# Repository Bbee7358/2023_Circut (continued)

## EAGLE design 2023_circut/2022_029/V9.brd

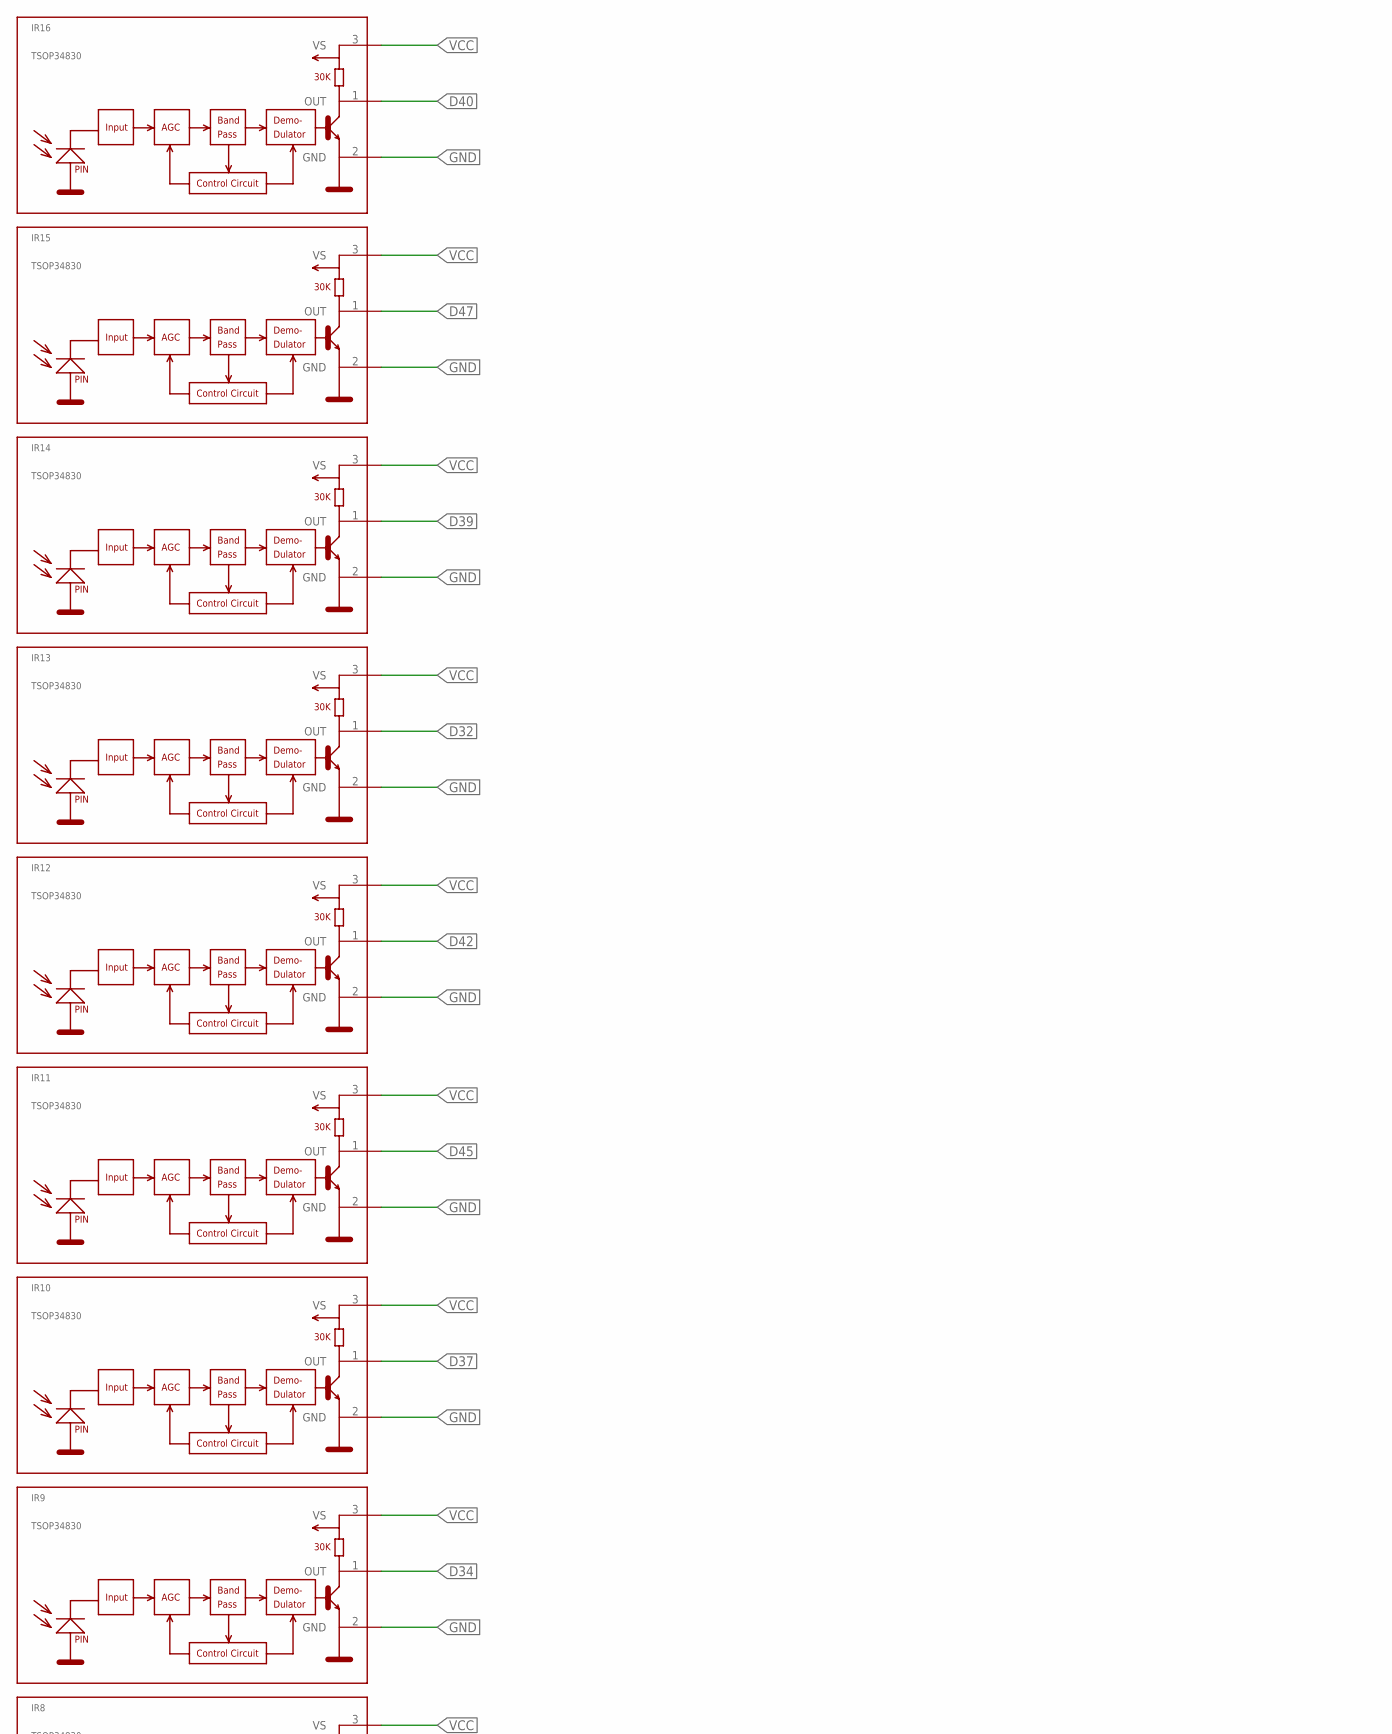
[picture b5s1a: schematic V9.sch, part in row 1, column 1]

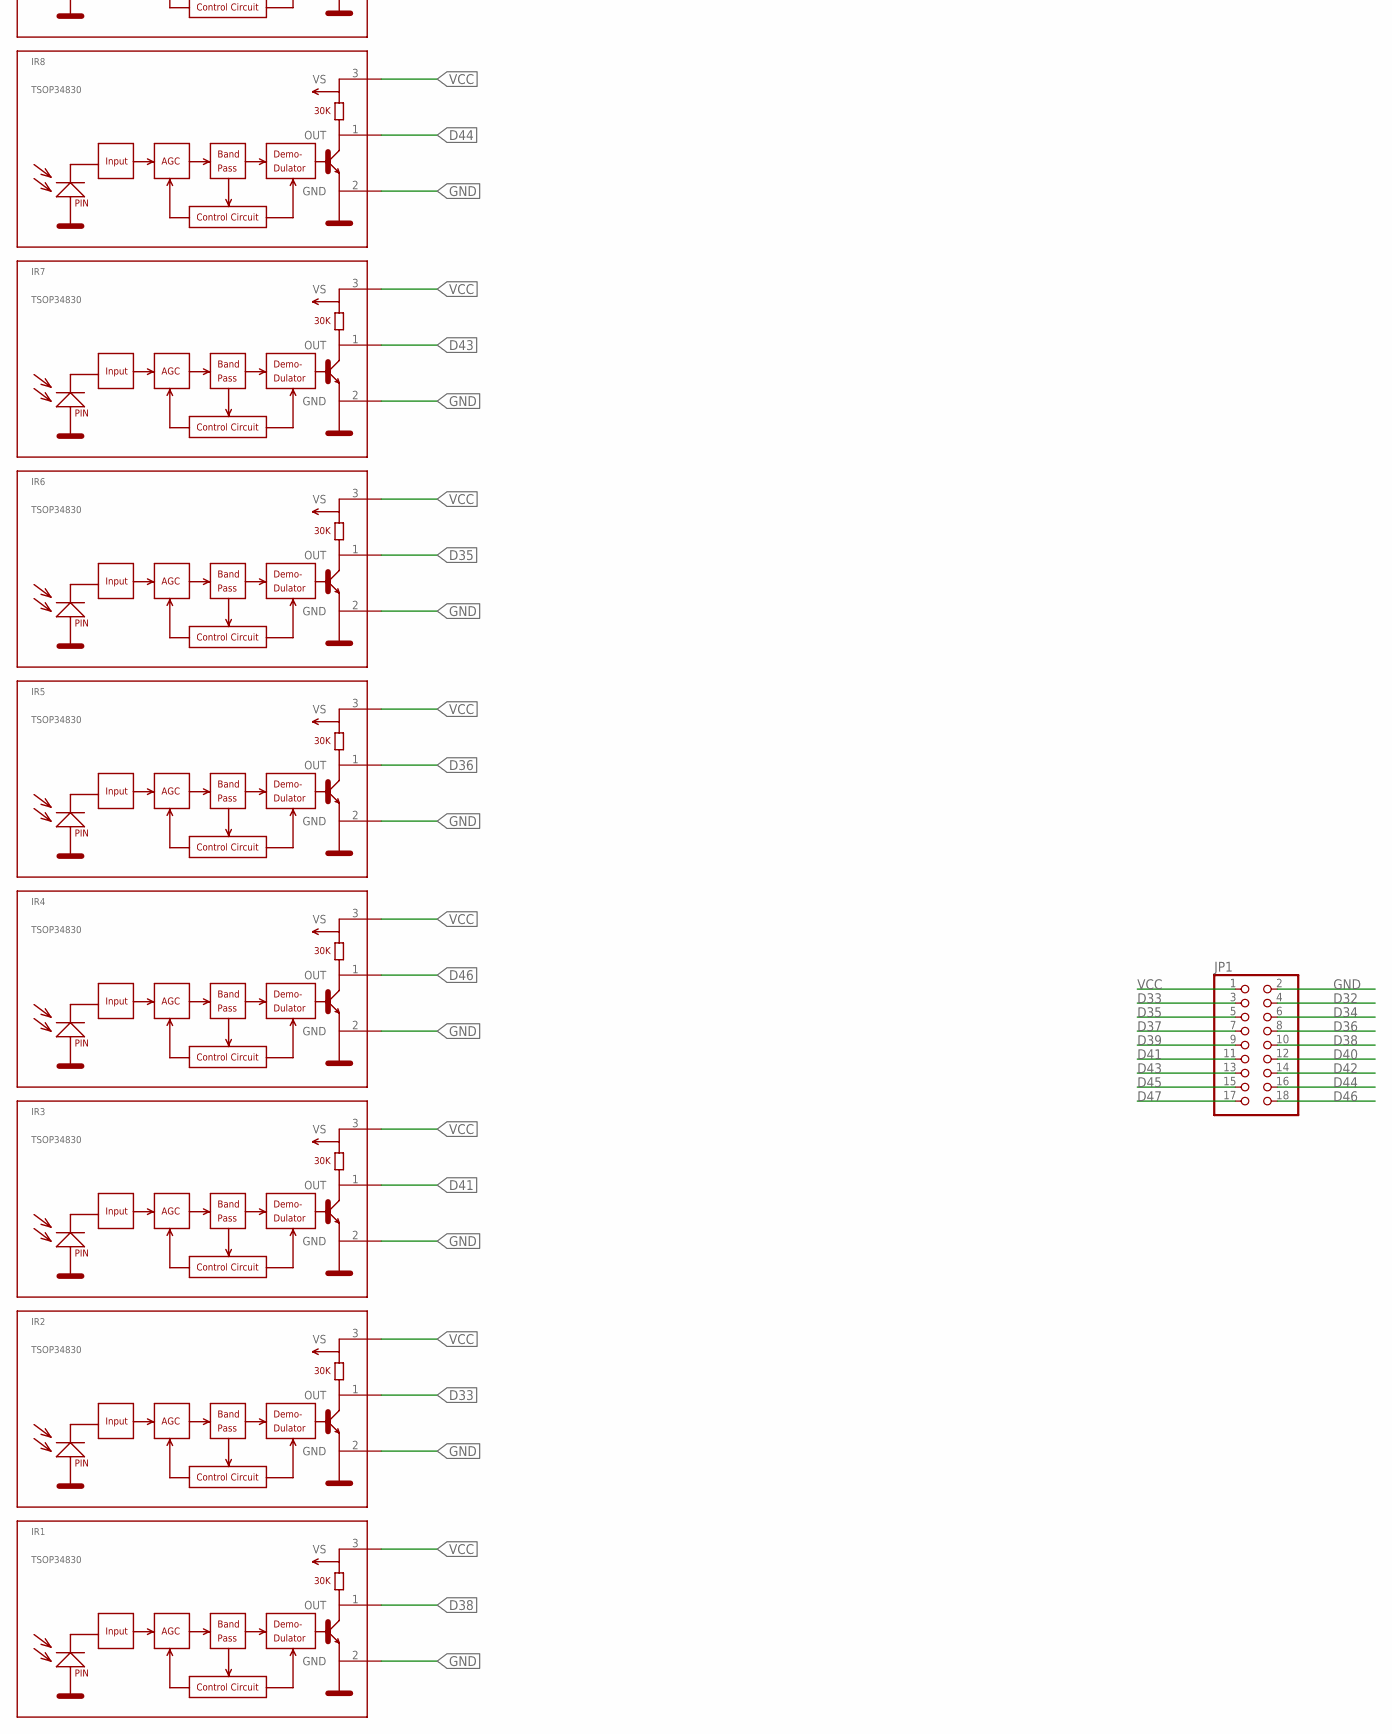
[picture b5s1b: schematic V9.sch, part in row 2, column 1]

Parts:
IR1, IR2, IR3, IR4, IR5, IR6, IR7, IR8, IR9, IR10, IR11, IR12, IR13, IR14, IR15, IR16: TSOP34830; TSOP348
JP1: PINHD-2X09_2.54; 2X09

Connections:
D32: IR13.1 (OUT), JP1.4
D33: IR2.1 (OUT), JP1.3
D34: IR9.1 (OUT), JP1.6
D35: IR6.1 (OUT), JP1.5
D36: IR5.1 (OUT), JP1.8
D37: IR10.1 (OUT), JP1.7
D38: IR1.1 (OUT), JP1.10
D39: IR14.1 (OUT), JP1.9
D40: IR16.1 (OUT), JP1.12
D41: IR3.1 (OUT), JP1.11
D42: IR12.1 (OUT), JP1.14
D43: IR7.1 (OUT), JP1.13
D44: IR8.1 (OUT), JP1.16
D45: IR11.1 (OUT), JP1.15
D46: IR4.1 (OUT), JP1.18
D47: IR15.1 (OUT), JP1.17
GND: IR1.2 (GND), IR2.2 (GND), IR3.2 (GND), IR4.2 (GND), IR5.2 (GND), IR6.2 (GND), IR7.2 (GND), IR8.2 (GND), IR9.2 (GND), IR10.2 (GND), IR11.2 (GND), IR12.2 (GND), IR13.2 (GND), IR14.2 (GND), IR15.2 (GND), IR16.2 (GND), JP1.2
VCC: IR1.3 (VS), IR2.3 (VS), IR3.3 (VS), IR4.3 (VS), IR5.3 (VS), IR6.3 (VS), IR7.3 (VS), IR8.3 (VS), IR9.3 (VS), IR10.3 (VS), IR11.3 (VS), IR12.3 (VS), IR13.3 (VS), IR14.3 (VS), IR15.3 (VS), IR16.3 (VS), JP1.1

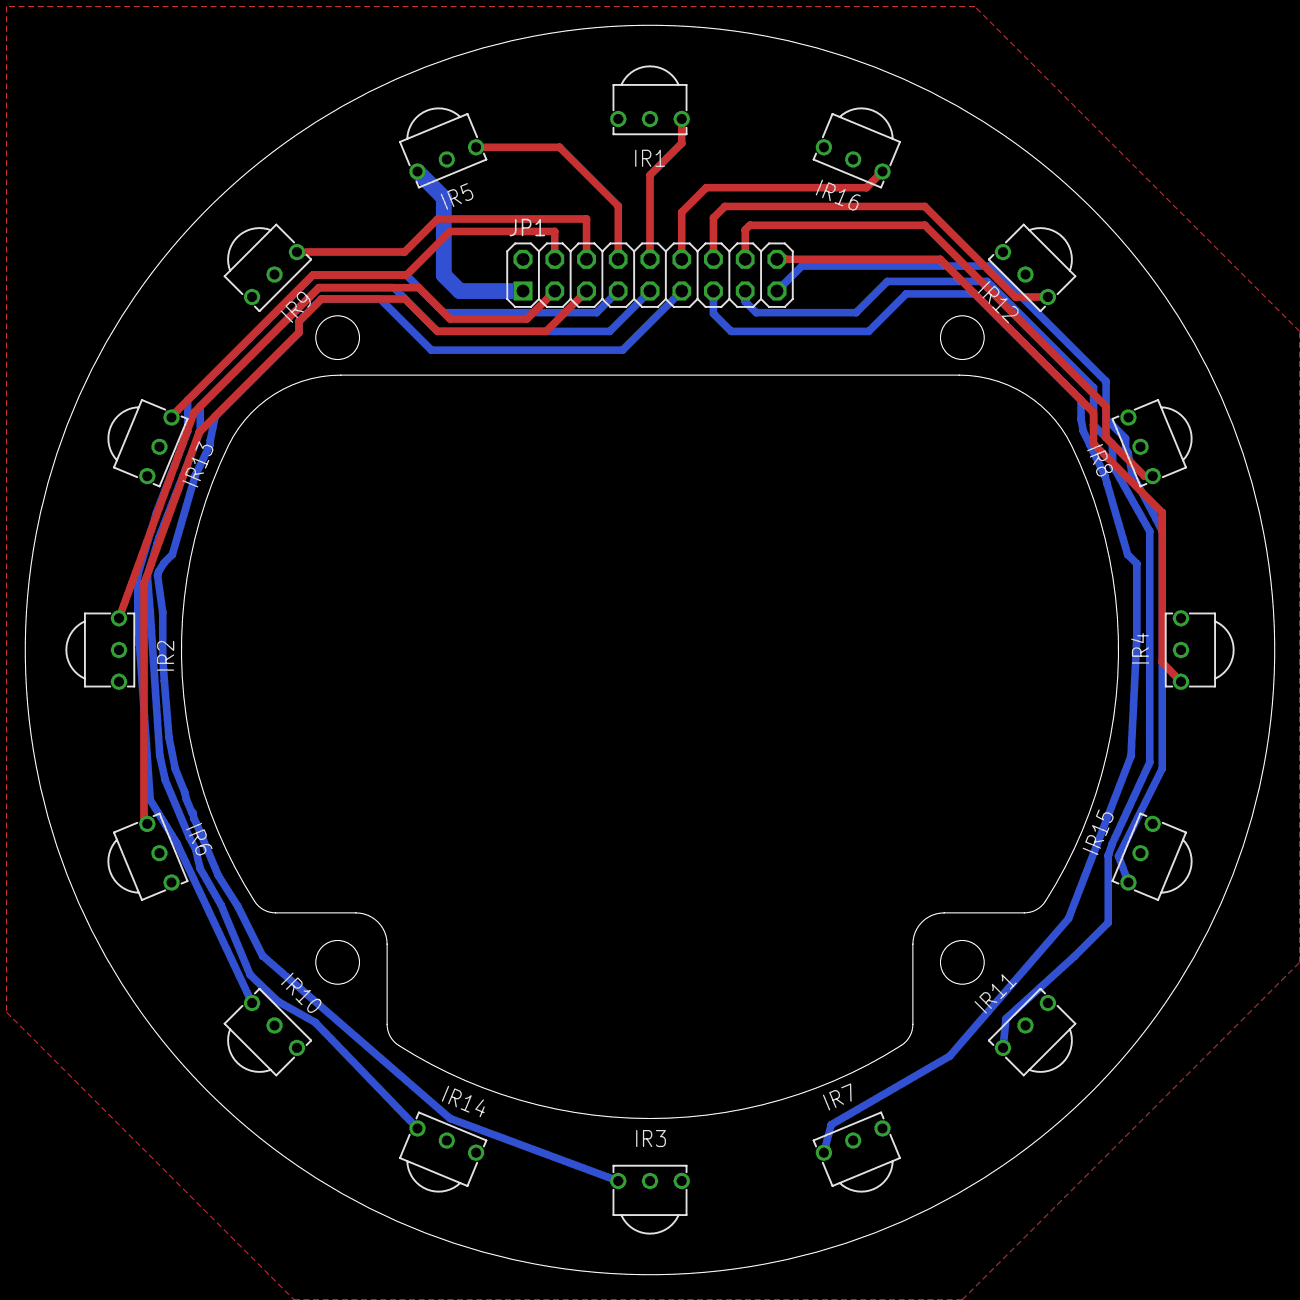
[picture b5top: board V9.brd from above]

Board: 2 copper layers, 100.0 x 100.0 mm, 17 parts (0 on the bottom side), 18 nets.

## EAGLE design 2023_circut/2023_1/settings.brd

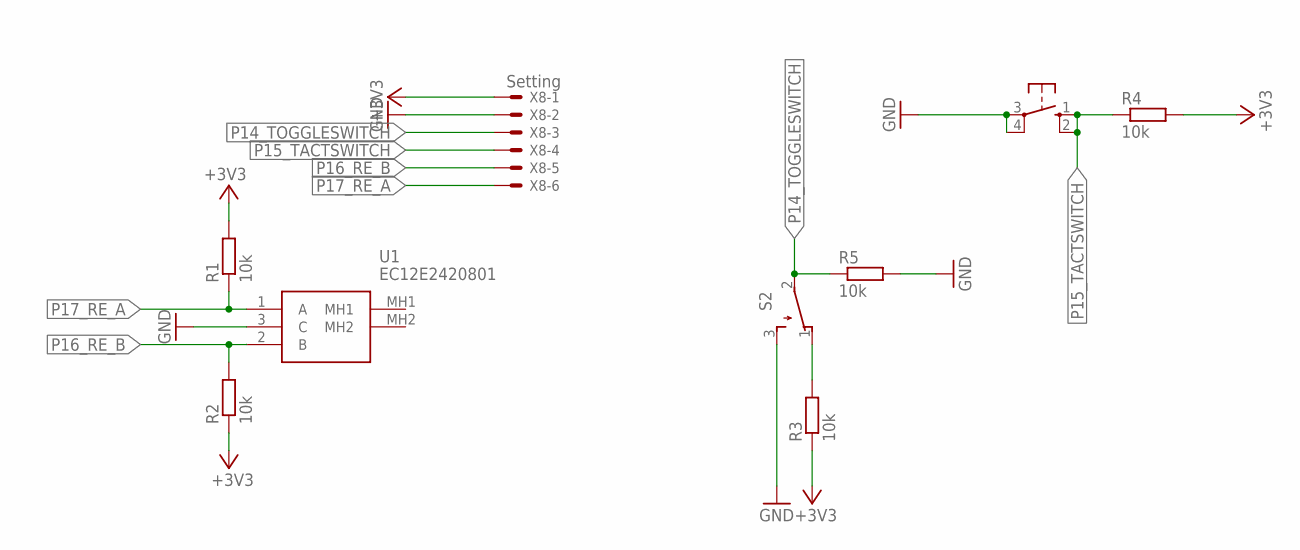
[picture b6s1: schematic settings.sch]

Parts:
R1, R2, R3, R4, R5: 10k; R0603
S1: 40-XX; B3F-40XX
S2: TL32PO; TL3XPO
U1: EC12E2420801
X8: Setting; JST-XH-06-PACKAGE-ROUND-PAD

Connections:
+3V3: R1.2, R2.1, R3.1, R4.2, X8.1
GND: R5.2, S1.3, S1.4 (P1), S2.3 (S), U1.3 (C), X8.2
unnamed: R3.2, S2.1 (O)
P14_TOGGLESWITCH: R5.1, S2.2, X8.3
P15_TACTSWITCH: R4.1, S1.1 (S), S1.2 (S1), X8.4
P16_RE_B: R2.2, U1.2 (B), X8.5
P17_RE_A: R1.1, U1.1 (A), X8.6

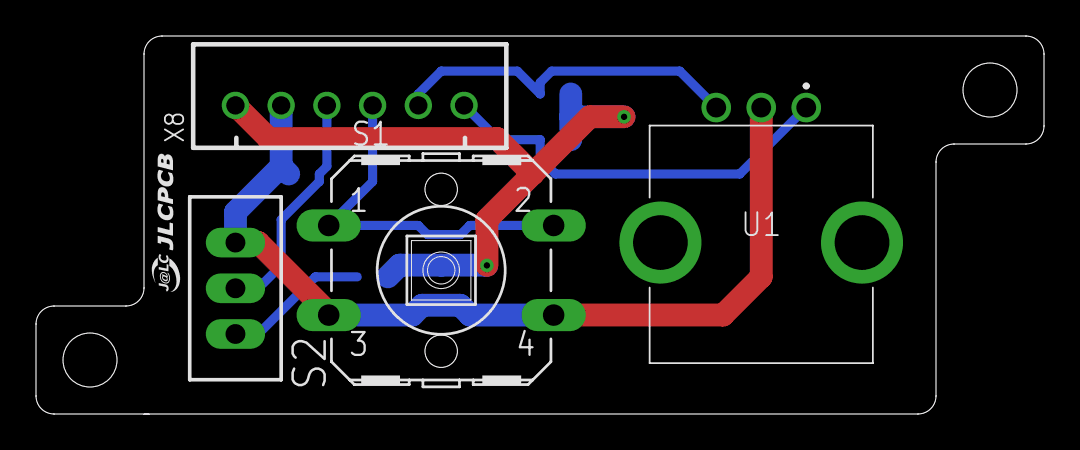
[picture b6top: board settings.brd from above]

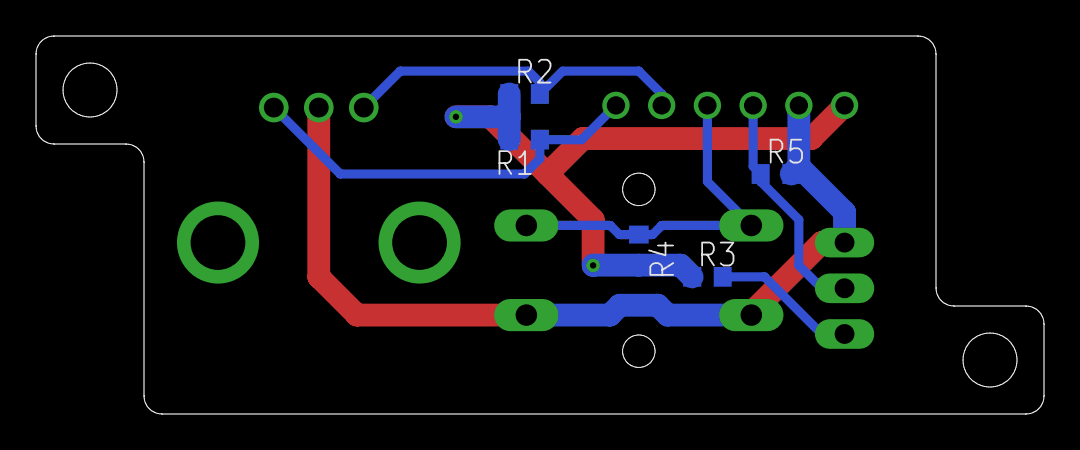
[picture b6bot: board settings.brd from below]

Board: 2 copper layers, 56.0 x 21.0 mm, 9 parts (5 on the bottom side), 7 nets.

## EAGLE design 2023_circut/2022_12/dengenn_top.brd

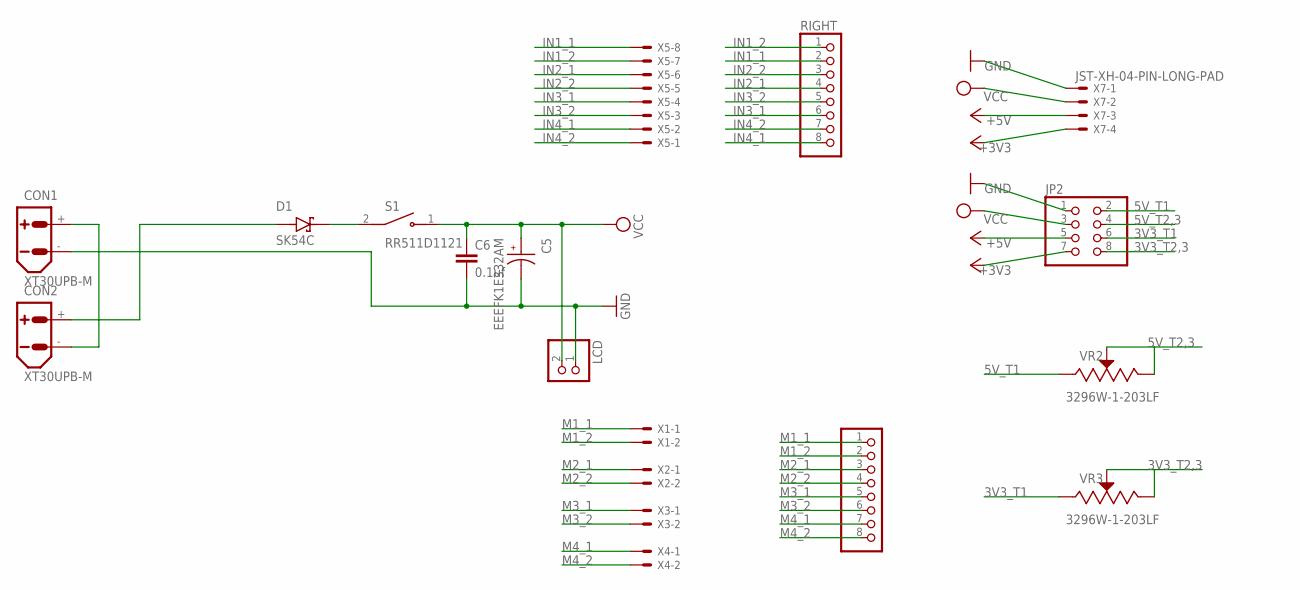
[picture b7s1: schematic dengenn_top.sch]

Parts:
C5: EEEFK1E332AM; CAP_EEEFK1E332AM
C6: 0.1uf; C0603
CON1, CON2: XT30UPB-M
D1: SK54C; DIOM6859X262N
JP2: PINHD-2X4; 2X04
LCD: PINHD-1X2; 1X02
LEFT: PINHD-1X8; 1X08
RIGHT: PINHD-1X8; 1X08
S1: RR511D1121; E-SWITCH_RR511D1121
VR2, VR3: 3296W-1-203LF; TRIM_3296W-1-203LF
X1, X2, X3, X4: JST-XH-02-PIN-LONG-PAD; JST-XH-02-PACKAGE-LONG-PAD
X5: JST-XH-08-PIN-ROUND-PAD; JST-XH-08-PACKAGE-ROUND-PAD
X7: JST-XH-04-PIN-LONG-PAD; JST-XH-04-PACKAGE-LONG-PAD

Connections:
3V3_T1: JP2.6, VR3.1 (CCW)
3V3_T2,3: JP2.8, VR3.2 (WIPER), VR3.3 (CW)
5V_T1: JP2.2, VR2.1 (CCW)
5V_T2,3: JP2.4, VR2.2 (WIPER), VR2.3 (CW)
+3V3: JP2.7, X7.4
+5V: JP2.5, X7.3
GND: C5.2, C6.2, CON1.-, JP2.1, LCD.1, X7.1
IN1_1: RIGHT.2, X5.8
IN1_2: RIGHT.1, X5.7
IN2_1: RIGHT.4, X5.6
IN2_2: RIGHT.3, X5.5
IN3_1: RIGHT.6, X5.4
IN3_2: RIGHT.5, X5.3
IN4_1: RIGHT.8, X5.2
IN4_2: RIGHT.7, X5.1
M1_1: LEFT.1, X1.1
M1_2: LEFT.2, X1.2
M2_1: LEFT.3, X2.1
M2_2: LEFT.4, X2.2
M3_1: LEFT.5, X3.1
M3_2: LEFT.6, X3.2
M4_1: LEFT.7, X4.1
M4_2: LEFT.8, X4.2
unnamed: CON1.+, CON2.-
unnamed: CON2.+, D1.A
unnamed: D1.C (K), S1.2 (COM)
VCC: C5.1, C6.1, JP2.3, LCD.2, S1.1 (NO), X7.2

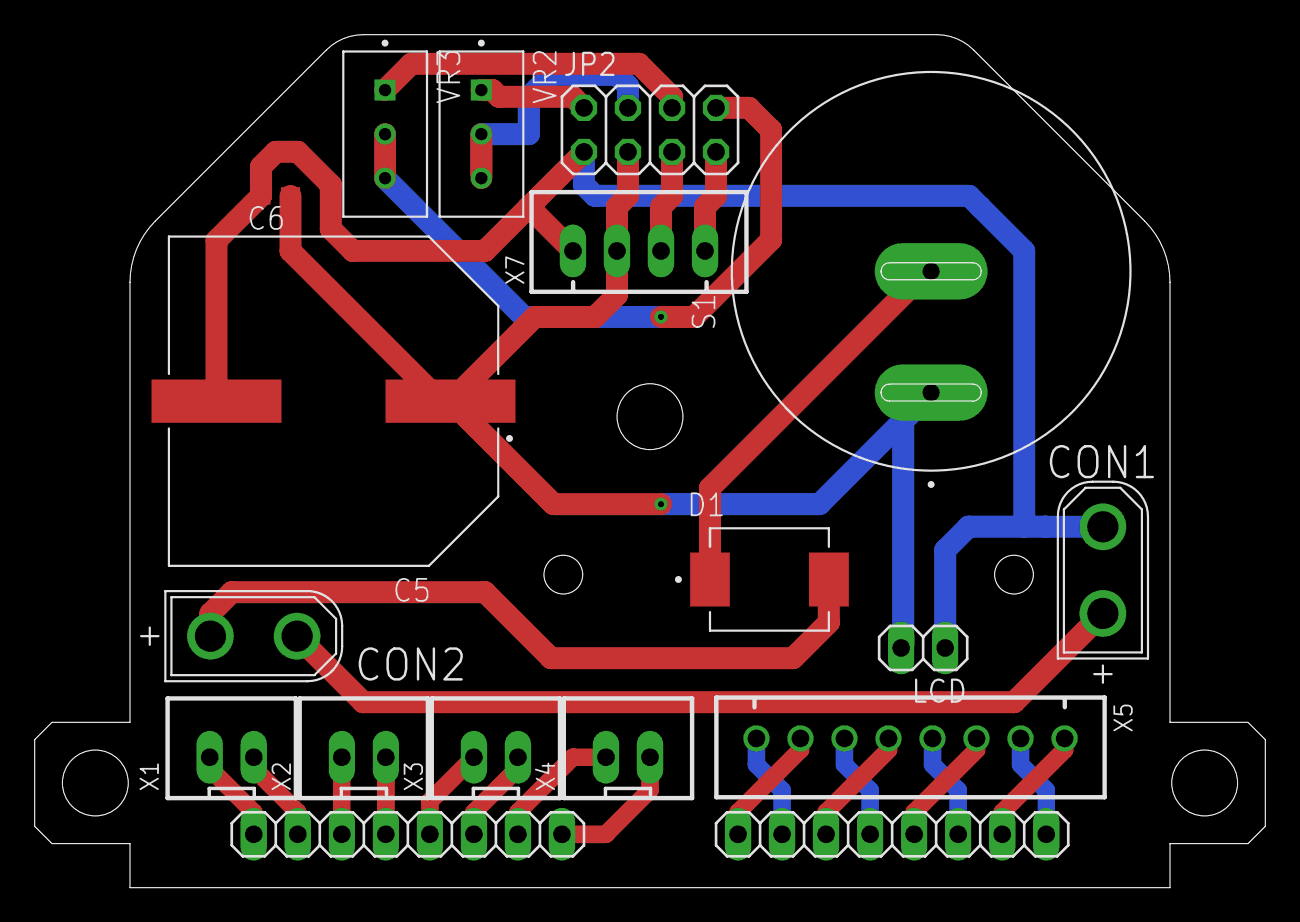
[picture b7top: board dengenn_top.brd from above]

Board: 2 copper layers, 71.0 x 49.2 mm, 18 parts (0 on the bottom side), 27 nets.

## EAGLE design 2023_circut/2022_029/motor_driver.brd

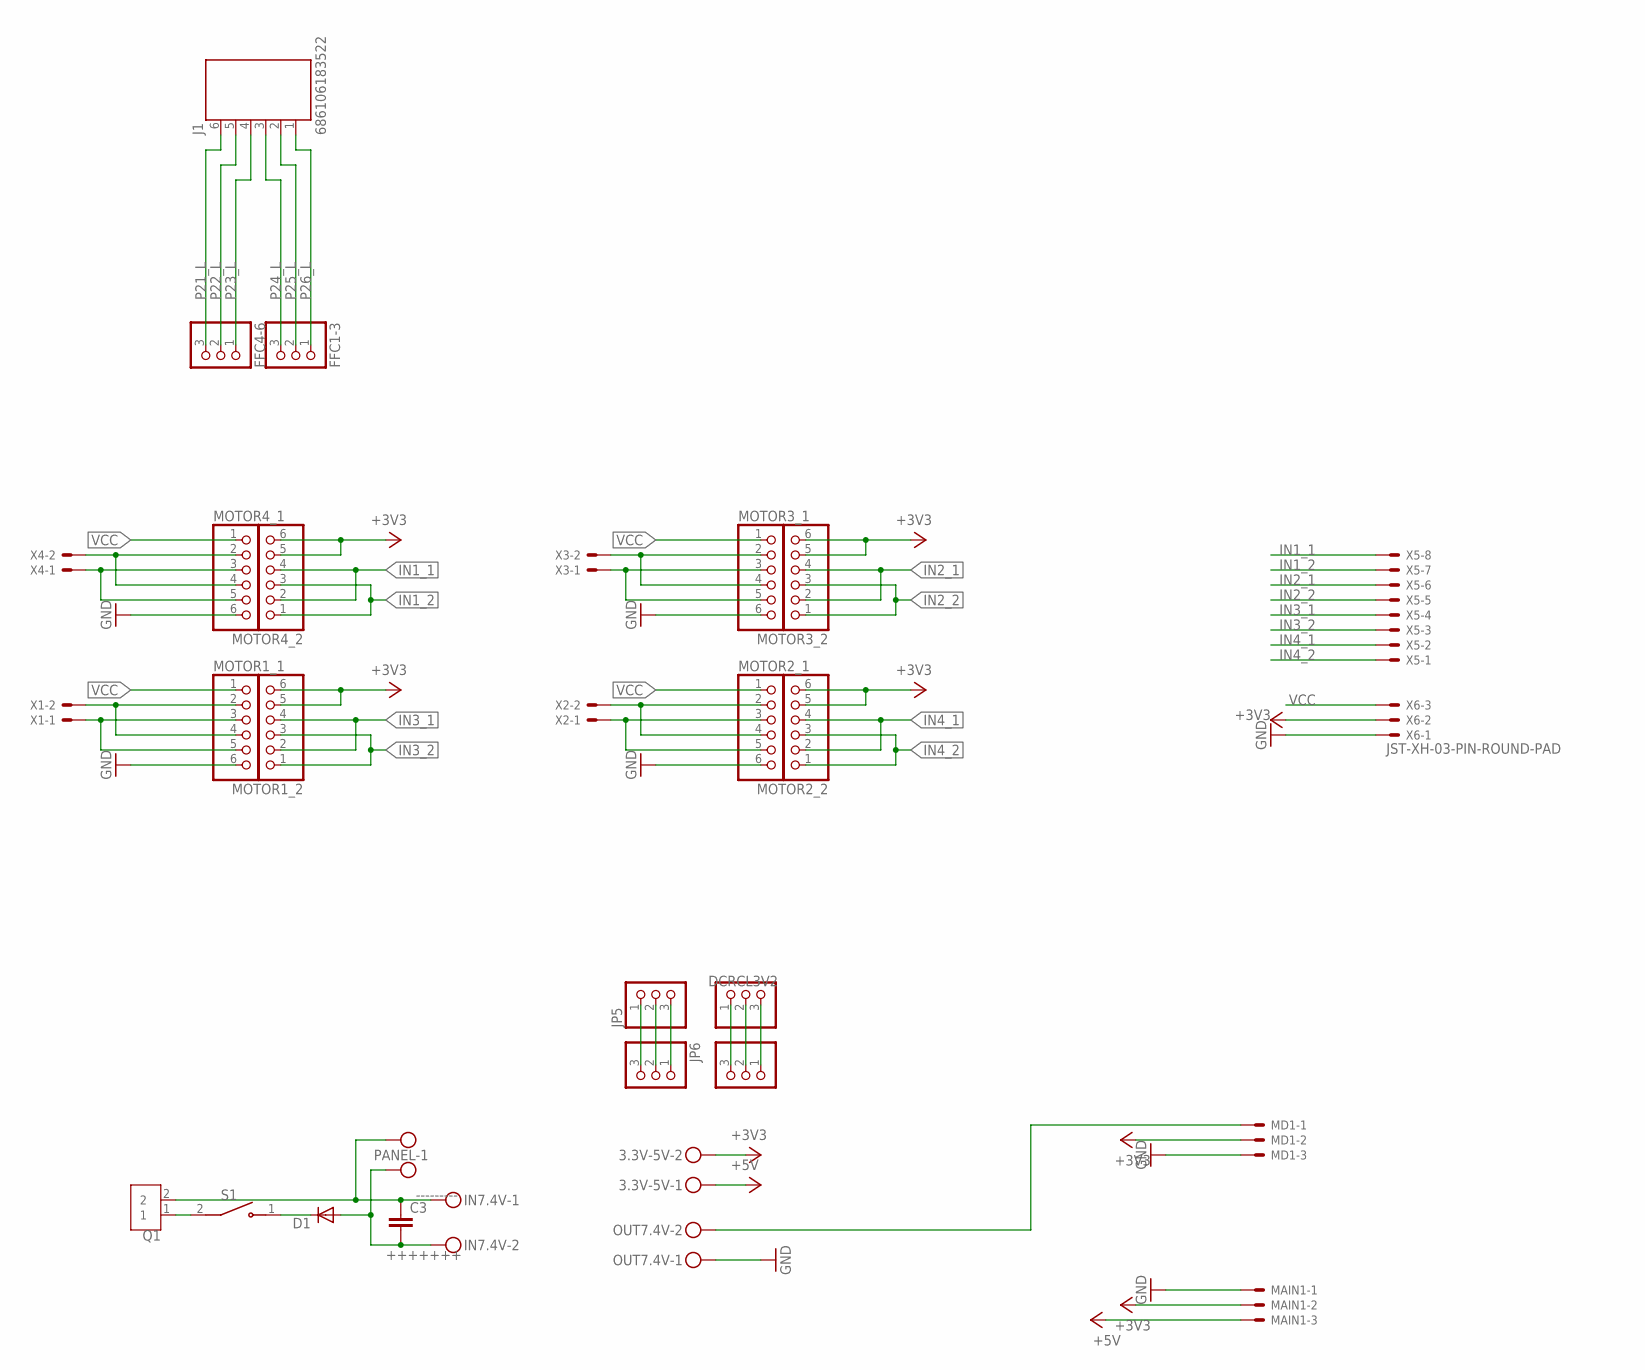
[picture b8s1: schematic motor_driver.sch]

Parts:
3.3V-5V: MKDSN1,5/2-5,08
C3: C-EU025-030X050; C025-030X050
D1: DIODE-SMC; SMC
DCRC3V1: PINHD-1X3; 1X03
DCRCL3V2: PINHD-1X3; 1X03
FFC1-3, FFC4-6: PINHD-1X03_2.54-S; 1X03-S
IN7.4V: MKDSN1,5/2-5,08
J1: 686106183522
JP5, JP6: PINHD-1X03_2.54-S; 1X03-S
MAIN1: JST-XH-03-PIN-ROUND-PAD; JST-XH-03-PACKAGE-ROUND-PAD
MD1: JST-XH-03-PIN-ROUND-PAD; JST-XH-03-PACKAGE-ROUND-PAD
MOTOR1_1, MOTOR1_2, MOTOR2_1, MOTOR2_2, MOTOR3_1, MOTOR3_2, MOTOR4_1, MOTOR4_2: PINHD-1X06_2.54-S; 1X06-S
OUT7.4V: MKDSN1,5/2-5,08
PANEL: MKDSN1,5/2-5,08
Q1: XT60_YELLOW; AMASS_XT60PB-M
S1: RR511D1121; E-SWITCH_RR511D1121
X1, X2, X3, X4: JST-XH-02-PIN-ROUND-PAD; JST-XH-02-PACKAGE-ROUND-PAD
X5: JST-XH-08-PIN-ROUND-PAD; JST-XH-08-PACKAGE-ROUND-PAD
X6: JST-XH-03-PIN-ROUND-PAD; JST-XH-03-PACKAGE-ROUND-PAD

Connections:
+3V3: 3.3V-5V.2, MAIN1.2, MD1.2, MOTOR1_2.5, MOTOR1_2.6, MOTOR2_2.5, MOTOR2_2.6, MOTOR3_2.5, MOTOR3_2.6, MOTOR4_2.5, MOTOR4_2.6, X6.2
+5V: 3.3V-5V.1, MAIN1.3
+++++++: C3.2, D1.A, IN7.4V.2, PANEL.2
---------: C3.1, IN7.4V.1, PANEL.1, Q1.2
GND: MAIN1.1, MD1.3, MOTOR1_1.6, MOTOR2_1.6, MOTOR3_1.6, MOTOR4_1.6, OUT7.4V.1, X6.1
IN1_1: MOTOR4_2.2, MOTOR4_2.4, X5.8
IN1_2: MOTOR4_2.1, MOTOR4_2.3, X5.7
IN2_1: MOTOR3_2.2, MOTOR3_2.4, X5.6
IN2_2: MOTOR3_2.1, MOTOR3_2.3, X5.5
IN3_1: MOTOR1_2.2, MOTOR1_2.4, X5.4
IN3_2: MOTOR1_2.1, MOTOR1_2.3, X5.3
IN4_1: MOTOR2_2.2, MOTOR2_2.4, X5.2
IN4_2: MOTOR2_2.1, MOTOR2_2.3, X5.1
unnamed: MOTOR1_1.2, MOTOR1_1.4, X1.2
unnamed: MOTOR1_1.3, MOTOR1_1.5, X1.1
unnamed: MOTOR2_1.2, MOTOR2_1.4, X2.2
unnamed: MOTOR2_1.3, MOTOR2_1.5, X2.1
unnamed: Q1.1, S1.2 (COM)
unnamed: DCRC3V1.3, DCRCL3V2.1
unnamed: JP5.1, JP6.3
unnamed: MOTOR3_1.2, MOTOR3_1.4, X3.2
unnamed: MOTOR3_1.3, MOTOR3_1.5, X3.1
unnamed: JP5.2, JP6.2
unnamed: MOTOR4_1.2, MOTOR4_1.4, X4.2
unnamed: MOTOR4_1.3, MOTOR4_1.5, X4.1
unnamed: DCRC3V1.2, DCRCL3V2.2
unnamed: DCRC3V1.1, DCRCL3V2.3
unnamed: JP5.3, JP6.1
unnamed: MD1.1, OUT7.4V.2
unnamed: D1.C, S1.1 (NO)
P21_L: FFC4-6.3, J1.6 (1)
P22_L: FFC4-6.2, J1.5 (2)
P23_L: FFC4-6.1, J1.4 (3)
P24_L: FFC1-3.3, J1.3 (4)
P25_L: FFC1-3.2, J1.2 (5)
P26_L: FFC1-3.1, J1.1 (6)
VCC: MOTOR1_1.1, MOTOR2_1.1, MOTOR3_1.1, MOTOR4_1.1, X6.3

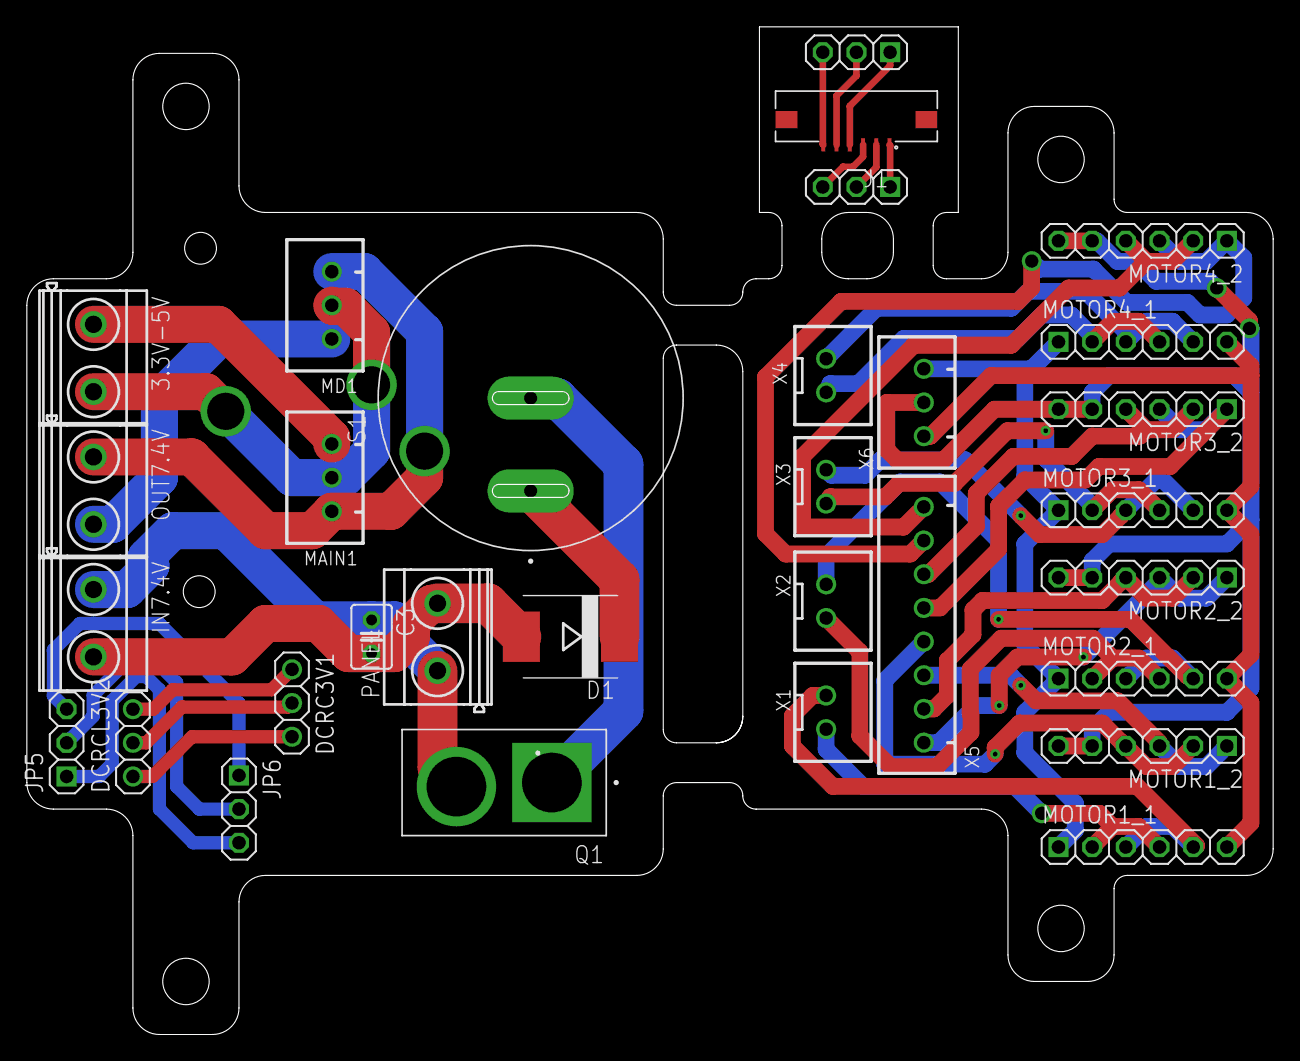
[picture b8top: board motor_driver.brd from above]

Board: 2 copper layers, 94.0 x 76.0 mm, 31 parts (0 on the bottom side), 37 nets.

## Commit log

2023-04-17 これが現時点での回路の最新版
